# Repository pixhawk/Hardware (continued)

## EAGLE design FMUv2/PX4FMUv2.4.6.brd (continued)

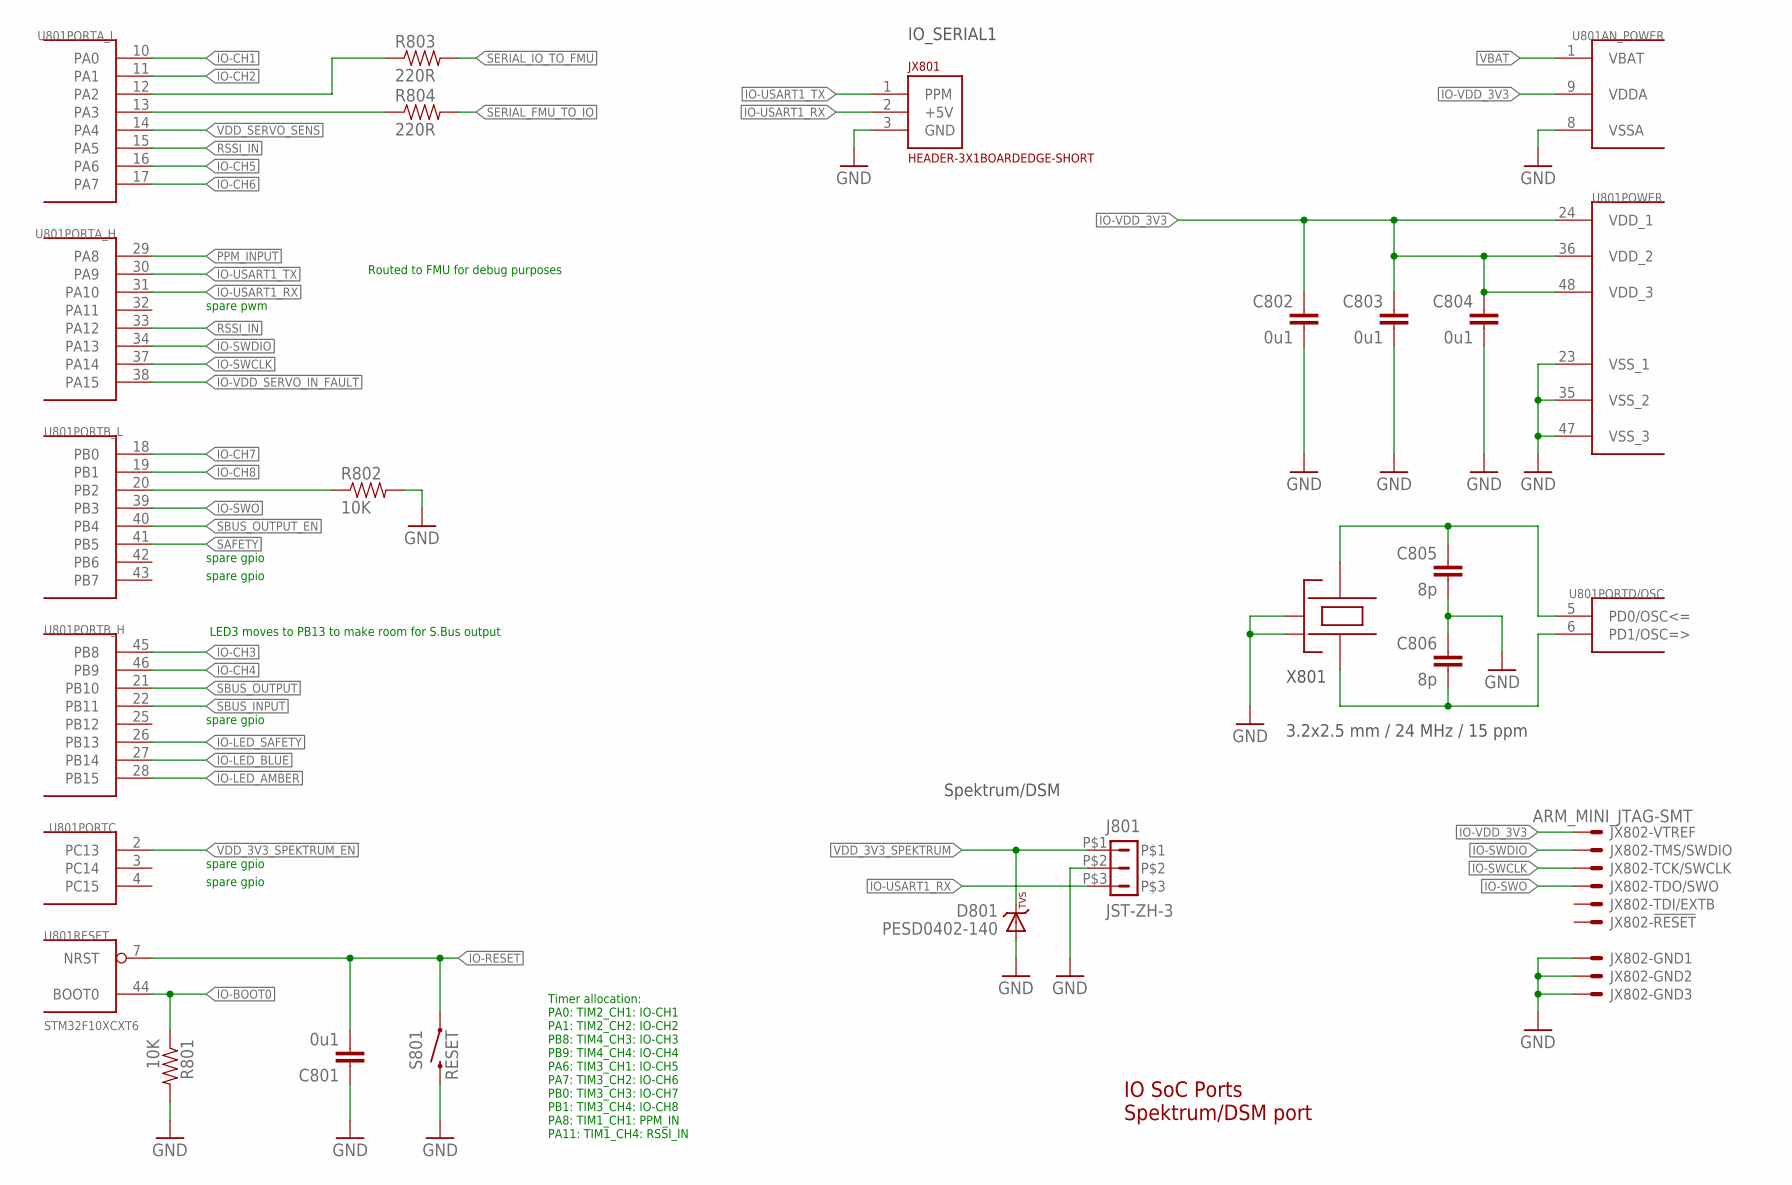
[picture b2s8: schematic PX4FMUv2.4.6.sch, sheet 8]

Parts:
C801, C802, C803, C804: 0u1; 0402-CAP; PARTNO CC0402ZRY5V7BB104
C805, C806: 8p; 0402-CAP; PARTNO C1005C0G1H080C
D801: PESD0402-140; 0402-TVS; PARTNO PESD0402-140
J801: JST-ZH-3; JST-ZH-SMT-VERTICAL; PARTNO B3B-ZR-SM4-TF (LF)(SN)(P)
JX801: HEADER-3X1BOARDEDGE-SHORT; HEADER_3X01_SMD_H_BOARD_EDGE_SHORT
JX802: ARM_MINI_JTAG-SMT; FTSH-105-01-XXX-DV-K; PARTNO M50-3900542
R801, R802: 10K; 0402-RES; PARTNO RC0402FR-0710KL
R803, R804: 220R; 0402-RES; PARTNO RC0402FR-07220RL
S801: RESET; EVQP7J01K; PARTNO EVQ-P7J01P
U801: STM32F10XCXT6; TQFP48; PARTNO STM32F100C8T6B
X801: 3.2x2.5 mm / 24 MHz / 15 ppm; OSCILLATOR-3.2X2.5; PARTNO NX3225SA-24.000000MHZ

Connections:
!IO-LED_AMBER: U801.28 (PB15); also elsewhere on the board
!IO-LED_BLUE: U801.27 (PB14); also elsewhere on the board
!IO-LED_SAFETY: U801.26 (PB13); also elsewhere on the board
!SBUS_OUTPUT_EN: U801.40 (PB4); also elsewhere on the board
GND: C801.P$1 (1), C802.P$2 (2), C803.P$2 (2), C804.P$2 (2), C805.P$2 (2), C806.P$1 (1), D801.A, J801.P$2, JX801.3 (GND), JX802.3, JX802.5, JX802.9, R801.P$2 (2), R802.P$2 (2), S801.B3 (2), U801.8 (VSSA), U801.23 (VSS_1), U801.35 (VSS_2), U801.47 (VSS_3), X801.2 (NC_2), X801.4 (NC_4); also elsewhere on the board
IO-!RESET: C801.P$2 (2), S801.A1 (1), U801.7 (NRST); also elsewhere on the board
IO-!VDD_SERVO_IN_FAULT: U801.38 (PA15); also elsewhere on the board
IO-BOOT0: R801.P$1 (1), U801.44 (BOOT0); also elsewhere on the board
IO-BOOT1: R802.P$1 (1), U801.20 (PB2)
IO-CH1: U801.10 (PA0); also elsewhere on the board
IO-CH2: U801.11 (PA1); also elsewhere on the board
IO-CH3: U801.45 (PB8); also elsewhere on the board
IO-CH4: U801.46 (PB9); also elsewhere on the board
IO-CH5: U801.16 (PA6); also elsewhere on the board
IO-CH6: U801.17 (PA7); also elsewhere on the board
IO-CH7: U801.18 (PB0); also elsewhere on the board
IO-CH8: U801.19 (PB1); also elsewhere on the board
IO-SWCLK: JX802.4, U801.37 (PA14)
IO-SWDIO: JX802.2, U801.34 (PA13)
IO-SWO: JX802.6, U801.39 (PB3)
IO-USART1_RX: J801.P$3, JX801.2 (+5V), U801.31 (PA10)
IO-USART1_TX: JX801.1 (PPM), U801.30 (PA9); also elsewhere on the board
IO-VDD_3V3: C802.P$1 (1), C803.P$1 (1), C804.P$1 (1), JX802.1, U801.9 (VDDA), U801.24 (VDD_1), U801.36 (VDD_2), U801.48 (VDD_3); also elsewhere on the board
unnamed: R803.P$1 (1), U801.12 (PA2)
unnamed: R804.P$1 (1), U801.13 (PA3)
unnamed: C806.P$2 (2), U801.6 (PD1/OSC=>), X801.1
unnamed: C805.P$1 (1), U801.5 (PD0/OSC<=), X801.3
PPM_INPUT: U801.29 (PA8); also elsewhere on the board
RSSI_IN: U801.15 (PA5), U801.33 (PA12); also elsewhere on the board
SAFETY: U801.41 (PB5); also elsewhere on the board
SBUS_INPUT: U801.22 (PB11); also elsewhere on the board
SBUS_OUTPUT: U801.21 (PB10); also elsewhere on the board
SERIAL_FMU_TO_IO: R804.P$2 (2); also elsewhere on the board
SERIAL_IO_TO_FMU: R803.P$2 (2); also elsewhere on the board
VBAT: U801.1 (VBAT); also elsewhere on the board
VDD_3V3_SPEKTRUM: D801.C, J801.P$1; also elsewhere on the board
VDD_3V3_SPEKTRUM_EN: U801.2 (PC13); also elsewhere on the board
VDD_SERVO_SENS: U801.14 (PA4); also elsewhere on the board

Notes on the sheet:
IO SoC Ports Spektrum/DSM port
LED3 moves to PB13 to make room for S.Bus output
Routed to FMU for debug purposes
IO_SERIAL1
Spektrum/DSM
Timer allocation: PA0: TIM2_CH1: IO-CH1 PA1: TIM2_CH2: IO-CH2 PB8: TIM4_CH3: IO-CH3 PB9: TIM4_CH4: IO-CH4 PA6: TIM3_CH1: IO-CH5 PA7: TIM3_CH2: IO-CH6 PB0: TIM3_CH3: IO-CH7 PB1: TIM3_CH4: IO-CH8 PA8: TIM1_CH1: PPM_IN PA11: TIM1_CH4: RSSI_IN
spare pwm
spare gpio

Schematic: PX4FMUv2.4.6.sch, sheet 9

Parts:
C901, C902, C903: 0u1; 0402-CAP; PARTNO CC0402ZRY5V7BB104
D901, D902, D903: PESD0402-140; 0402-TVS; PARTNO PESD0402-140
D904: MSS1P4-M3; MICROSMP; PARTNO MSS1P4-M3/89A
J901: HEADER-3X163X16RA; 3X16RA
L901: KNH16C104DA5TS; KYOCERA-KNH16-DA; PARTNO KNH16C104DA5TS
R901: 10K; 0402-RES; PARTNO RC0402FR-0710KL
R902, R903, R904, R905, R906, R907, R908, R909, R910, R911, R912, R913, R914, R915, R916, R917: 220R; 0402-RES; PARTNO RC0402FR-07220RL
R918, R919, R922: 10K/0.1%; 0402-RES; PARTNO ERA-2AEB103X
U901, U902: TXS0108QFN20; QFN20-RGY; PARTNO TXS0108ERGYR
U903: 74LVC2G240; TSSOP8_SOT505-2; PARTNO 74LVC2G240DP,125

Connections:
!SBUS_OUTPUT_EN: U903.7 (!2OE); also elsewhere on the board
FMU-CH1: U901.7 (A6); also elsewhere on the board
FMU-CH1-PROT: J901.46, R913.P$2 (2)
FMU-CH2: U901.6 (A5); also elsewhere on the board
FMU-CH3: U901.5 (A4); also elsewhere on the board
FMU-CH4: U901.4 (A3); also elsewhere on the board
FMU-CH5: U901.3 (A2); also elsewhere on the board
FMU-CH6: U901.1 (A1); also elsewhere on the board
FMU-CH6-PROT: J901.31, R902.P$2 (2)
FMU-VDD_3V3: C902.P$1 (1), U901.2 (VCCA), U901.10 (OE), U901.19 (VCCB); also elsewhere on the board
GND: C901.P$2 (2), C902.P$2 (2), C903.P$2 (2), D901.A, D902.A, D903.A, J901.3, J901.6, J901.9, J901.12, J901.15, J901.18, J901.21, J901.24, J901.27, J901.30, J901.33, J901.36, J901.39, J901.42, J901.45, J901.48, L901.P$3, L901.P$4, L901.P$5, R919.P$1 (1), U901.11 (GND), U902.11 (GND), U903.1 (!1OE), U903.4 (GND); also elsewhere on the board
IO-CH1: U902.9 (A8); also elsewhere on the board
IO-CH1-PROT: J901.28, R917.P$2 (2)
IO-CH2: U902.8 (A7); also elsewhere on the board
IO-CH3: U902.7 (A6); also elsewhere on the board
IO-CH4: U902.6 (A5); also elsewhere on the board
IO-CH5: U902.5 (A4); also elsewhere on the board
IO-CH6: U902.4 (A3); also elsewhere on the board
IO-CH7: U902.3 (A2); also elsewhere on the board
IO-CH8: U902.1 (A1); also elsewhere on the board
IO-CH8-PROT: J901.7, R905.P$2 (2)
IO-VDD_3V3: C901.P$1 (1), C903.P$1 (1), U902.2 (VCCA), U902.10 (OE), U902.19 (VCCB), U903.8 (VCC); also elsewhere on the board
IO-VDD_5V5: J901.2; also elsewhere on the board
unnamed: R918.P$2 (2), R922.P$1 (1)
unnamed: J901.10, R914.P$2 (2)
unnamed: D902.C, R901.P$2 (2), R910.P$1 (1), U903.3 (2Y)
unnamed: R905.P$1 (1), U902.20 (B1)
unnamed: R914.P$1 (1), U902.18 (B2)
unnamed: R906.P$1 (1), U902.17 (B3)
unnamed: R915.P$1 (1), U902.16 (B4)
unnamed: R907.P$1 (1), U902.15 (B5)
unnamed: R916.P$1 (1), U902.14 (B6)
unnamed: R908.P$1 (1), U902.13 (B7)
unnamed: R917.P$1 (1), U902.12 (B8)
unnamed: R902.P$1 (1), U901.20 (B1)
unnamed: R911.P$1 (1), U901.18 (B2)
unnamed: R903.P$1 (1), U901.17 (B3)
unnamed: R912.P$1 (1), U901.16 (B4)
unnamed: R904.P$1 (1), U901.15 (B5)
unnamed: R913.P$1 (1), U901.14 (B6)
unnamed: J901.34, R911.P$2 (2)
unnamed: J901.13, R906.P$2 (2)
unnamed: J901.16, R915.P$2 (2)
unnamed: J901.19, R907.P$2 (2)
unnamed: J901.22, R916.P$2 (2)
unnamed: J901.25, R908.P$2 (2)
unnamed: J901.37, R903.P$2 (2)
unnamed: J901.40, R912.P$2 (2)
unnamed: J901.43, R904.P$2 (2)
unnamed: J901.4, R910.P$2 (2)
unnamed: D903.C, D904.CATHODE (C), L901.P$1
PPM-SBUS-PROT: J901.1, R909.P$2 (2)
PPM_INPUT: D901.C, R909.P$1 (1), U903.2 (1A); also elsewhere on the board
RSSI_IN: R901.P$1 (1); also elsewhere on the board
SBUS_INPUT: U903.6 (1Y); also elsewhere on the board
SBUS_OUTPUT: U903.5 (2A); also elsewhere on the board
VDD_SERVO: D904.ANODE (A), J901.5, J901.8, J901.11, J901.14, J901.17, J901.20, J901.23, J901.26, J901.29, J901.32, J901.35, J901.38, J901.41, J901.44, J901.47, R922.P$2 (2); also elsewhere on the board
VDD_SERVO_IN: L901.P$2; also elsewhere on the board
VDD_SERVO_SENS: R918.P$1 (1), R919.P$2 (2); also elsewhere on the board

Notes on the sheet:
Servo Header S.Bus interface
S.Bus in/out
Servo outputs

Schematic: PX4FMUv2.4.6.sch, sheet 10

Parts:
C1001: 10u/25V; 0805-CAP; PARTNO CL21A106KAYNNNE
C1002: 10n; 0402-CAP; PARTNO CC0402KRX7R7BB103
C1003: 1u; 0603-CAP; PARTNO CC0603ZRY5V7BB105
C1004: 10u; 0603-CAP; PARTNO C1608X5R1A106K080AC
C1005: 0u1; 0402-CAP; PARTNO CC0402ZRY5V7BB104
C1008: 2u2; 0402-CAP; PARTNO C1005X6S1C225K050BC
D1001: PMEG2005CT; SOT23-3; PARTNO PMEG2005CT
F1001: 0ZCA0035FF2G; PTC-1206; PARTNO 0ZCA0035FF2G
R1001: 100K; 0402-RES; PARTNO RC0402FR-07100KL
R1002: 10K; 0402-RES; PARTNO RC0402FR-0710KL
U1001: BQ24313; QFN8-DSG; PARTNO BQ24313DSGT
U1002: MIC5332; MLF-8-EPAD; PARTNO MIC5332-SSYMT

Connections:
GND: C1001.P$2 (2), C1002.P$2 (2), C1003.P$2 (2), C1004.P$2 (2), C1005.P$2 (2), C1008.P$2 (2), R1001.P$1 (1), R1002.P$1 (1), U1001.2 (VSS), U1001.5 (!CE), U1001.6 (VBAT), U1001.GND (VSS), U1001.P$2 (VSS), U1001.P$3 (VSS), U1002.2 (GND), U1002.GND; also elsewhere on the board
IO-!RESET: U1002.3 (POR2); also elsewhere on the board
IO-!VDD_SERVO_IN_FAULT: U1001.4 (!FAULT); also elsewhere on the board
IO-VDD_3V3: C1003.P$1 (1), C1004.P$1 (1), U1002.7 (VOUT2); also elsewhere on the board
IO-VDD_5V5: C1001.P$1 (1), C1005.P$1 (1), D1001.3 (CC), U1002.1 (VIN), U1002.4 (EN2); also elsewhere on the board
unnamed: D1001.2 (A2), U1001.8 (OUT)
unnamed: R1001.P$2 (2), U1001.7 (ILIM)
unnamed: D1001.1 (A1), F1001.2
unnamed: C1002.P$1 (1), U1002.6 (CSET)
VDD_3V3_SPEKTRUM: C1008.P$1 (1), U1002.8 (VOUT1); also elsewhere on the board
VDD_3V3_SPEKTRUM_EN: R1002.P$2 (2), U1002.5 (EN1); also elsewhere on the board
VDD_5V_IN: F1001.1; also elsewhere on the board
VDD_SERVO_IN: U1001.1 (IN); also elsewhere on the board

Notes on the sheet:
Dual supply from servo rail and FMU 5V rail
Current limit = 25 / Rilim (current in A, R in kOhms) 100K = 250mA
IO Power Supply
Reset output 1s / uF 10n = 10ms delay from power good to reset de-asserted.
Output voltage limited to 5.5V for input voltages up to 10.5V; output switches off at higher input voltages.

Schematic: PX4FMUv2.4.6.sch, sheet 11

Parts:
C1101, C1102, C1103: 22u/25V; 0805-CAP; PARTNO CL21A226MAQNNNE
C1104: 100u; 1206-CAP; PARTNO C3216X5R1A107M160AC
C1105, C1106, C1107: 0u1; 0402-CAP; PARTNO C1005X7R1E104K050BB
C1108, C1109, C1110: 10p/25V; 0402-CAP; PARTNO C0402C100J3GACTU
J601: DF13C-6P-1.25V; PARTNO DF13C-6P-1.25V(20)
L1101, L1102: KNH16C104DA5TS; KYOCERA-KNH16-DA; PARTNO KNH16C104DA5TS
R1101, R1102: 10K/0.1%; 0402-RES; PARTNO ERA-2AEB103X
R1103, R1104: 1M; 0402-RES; PARTNO RC0402FR-071ML
R1105, R1109, R1112: 453K; 0402-RES; PARTNO RMCF0402FT453K
R1106, R1110, R1113: 56K; 0402-RES; PARTNO ERA-2AEB563X
R1107, R1111, R1114: 105K; 0402-RES; PARTNO ERJ-2RKF1053X
R1115: 0R; 0402-RES; PARTNO ERJ-2GE0R00X
RN1101: 1M; EXB28V; PARTNO EXB-28V105JX
U1101: LTC4417; MO-220; PARTNO LTC4417IUF#PBF
U1102, U1103, U1104: NTHD4102PT1G; 1206-8; PARTNO NTHD4102PT1G

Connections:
!VBUS_VALID: RN1101.2 (1), U1101.P$9 (!VALID3); also elsewhere on the board
!VDD_BRICK_VALID: RN1101.4 (1), U1101.P$7 (!VALID1); also elsewhere on the board
!VDD_SERVO_VALID: RN1101.3 (1), U1101.P$8 (!VALID2); also elsewhere on the board
BATT_CURRENT_SENS: R1101.P$1 (1); also elsewhere on the board
BATT_CURRENT_SENS_PROT: J601.3, L1101.P$1, R1104.P$1 (1)
BATT_VOLTAGE_SENS: R1102.P$1 (1); also elsewhere on the board
BATT_VOLTAGE_SENS_PROT: J601.4, L1102.P$1, R1103.P$1 (1)
GND: C1101.P$2 (2), C1102.P$2 (2), C1103.P$2 (2), C1104.P$2 (2), C1105.P$2 (2), C1106.P$2 (2), C1107.P$2 (2), C1108.P$2 (2), C1109.P$2 (2), C1110.P$2 (2), J601.5, J601.6, L1101.P$3, L1101.P$4, L1101.P$5, L1102.P$3, L1102.P$4, L1102.P$5, R1103.P$2 (2), R1104.P$2 (2), R1107.P$2 (2), R1111.P$2 (2), R1114.P$2 (2), R1115.P$1 (1), U1101.P$10 (GND), U1101.P$25 (GND); also elsewhere on the board
unnamed: C1108.P$1 (1), R1105.P$2 (2), R1106.P$1 (1), U1101.P$1 (UV1)
unnamed: R1106.P$2 (2), R1107.P$1 (1), U1101.P$2 (OV1)
unnamed: C1109.P$1 (1), R1109.P$2 (2), R1110.P$1 (1), U1101.P$3 (UV2)
unnamed: R1110.P$2 (2), R1111.P$1 (1), U1101.P$4 (OV2)
unnamed: R1113.P$2 (2), R1114.P$1 (1), U1101.P$6 (OV3)
unnamed: C1110.P$1 (1), R1112.P$2 (2), R1113.P$1 (1), U1101.P$5 (UV3)
unnamed: C1105.P$1 (1), U1101.P$18 (VS1), U1102.P$1 (S), U1102.P$3 (S)
unnamed: L1102.P$2, R1102.P$2 (2)
unnamed: L1101.P$2, R1101.P$2 (2)
unnamed: R1115.P$2 (2), U1101.P$24 (HYS)
unnamed: C1106.P$1 (1), U1101.P$16 (VS2), U1103.P$1 (S), U1103.P$3 (S)
unnamed: C1107.P$1 (1), U1101.P$14 (VS3), U1104.P$1 (S), U1104.P$3 (S)
unnamed: U1101.P$13 (G3), U1104.P$2 (G), U1104.P$4 (G)
unnamed: U1101.P$15 (G2), U1103.P$2 (G), U1103.P$4 (G)
unnamed: U1101.P$17 (G1), U1102.P$2 (G), U1102.P$4 (G)
VBUS: C1103.P$1 (1), R1112.P$1 (1), U1101.P$19 (V3), U1104.P$7 (D), U1104.P$8 (D); also elsewhere on the board
VDD_5V_BRICK: C1101.P$1 (1), J601.1, J601.2, R1105.P$1 (1), U1101.P$21 (V1), U1102.P$7 (D), U1102.P$8 (D); also elsewhere on the board
VDD_5V_IN: C1104.P$1 (1), RN1101.5 (2), RN1101.6 (2), RN1101.7 (2), U1101.P$12 (VOUT), U1102.P$5 (D), U1102.P$6 (D), U1103.P$5 (D), U1103.P$6 (D), U1104.P$5 (D), U1104.P$6 (D); also elsewhere on the board
VDD_SERVO: C1102.P$1 (1), R1109.P$1 (1), U1101.P$20 (V2), U1103.P$7 (D), U1103.P$8 (D); also elsewhere on the board

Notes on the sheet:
Power source selector
Resistors picked so that undervoltage lockout starts at 4.0V and overvoltage lockout at 5.75V. Use 1% or better accuracy!
POWER PATH CONTROLLER: Does enable output if valid for continous 256 ms
XXX Check all input pins are 5V tolerant. Hooking this up to a 3.3V rail would make the lines non-readable during power-up sequencing

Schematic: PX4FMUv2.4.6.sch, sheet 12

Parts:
!VBUS_VALID: PAD.04; PAD.04X.04; PARTNO *
!VDD_BRICK_VALID: PAD.04; PAD.04X.04; PARTNO *
!VDD_SERVO_VALID: PAD.04; PAD.04X.04; PARTNO *
ADC_PR: PAD.04; PAD.04X.04; PARTNO *
CAN_H: PAD.04; PAD.04X.04; PARTNO *
CAN_L: PAD.04; PAD.04X.04; PARTNO *
FMU-BOOT1101: PAD.04; PAD.04X.04; PARTNO *
GND, GND.: PAD.04; PAD.04X.04; PARTNO *
IO-BOOT1101: PAD.04; PAD.04X.04; PARTNO *
JP1, JP2: FIDUCIAL1.5X3; FIDUCIAL-1.5X3; PARTNO *
M3_MOUNT1101, M3_MOUNT1102, M3_MOUNT1103, M3_MOUNT1104: MOUNT-HOLE3.1MM; MOUNT-HOLE3.1; PARTNO *
OSHW_LOGO: OSHW-LOGOS; OSHW-LOGO-S; PARTNO *
S1RX, S1TX, S2RX, S2TX, S3RX, S3TX, S4RX, S4TX, S5_RX, S5_TX: PAD.04; PAD.04X.04; PARTNO *
VBUS: PAD.04; PAD.04X.04; PARTNO *
VDDA_3V1101: PAD.04; PAD.04X.04; PARTNO *
VDD_3V1101, VDD_5V_BRICK, VDD_5V_IN: PAD.04; PAD.04X.04; PARTNO *
VDD_SERVO: PAD.04; PAD.04X.04; PARTNO *

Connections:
!VBUS_VALID: !VBUS_VALID.P$1; also elsewhere on the board
!VDD_BRICK_VALID: !VDD_BRICK_VALID.P$1; also elsewhere on the board
!VDD_SERVO_VALID: !VDD_SERVO_VALID.P$1; also elsewhere on the board
CAN_H: CAN_H.P$1; also elsewhere on the board
CAN_L: CAN_L.P$1; also elsewhere on the board
FMU-BOOT0: FMU-BOOT1101.P$1; also elsewhere on the board
FMU-VDD_3V3: VDD_3V1101.P$1; also elsewhere on the board
GND: GND.P$1, GND..P$1; also elsewhere on the board
IO-BOOT0: IO-BOOT1101.P$1; also elsewhere on the board
PRESSURE_SENS_IN: ADC_PR.P$1; also elsewhere on the board
SERIAL1_RX: S1RX.P$1; also elsewhere on the board
SERIAL1_TX: S1TX.P$1; also elsewhere on the board
SERIAL2_RX: S2RX.P$1; also elsewhere on the board
SERIAL2_TX: S2TX.P$1; also elsewhere on the board
SERIAL3_RX: S3RX.P$1; also elsewhere on the board
SERIAL3_TX: S3TX.P$1; also elsewhere on the board
SERIAL4_RX: S4RX.P$1; also elsewhere on the board
SERIAL4_TX: S4TX.P$1; also elsewhere on the board
SERIAL5_RX: S5_RX.P$1; also elsewhere on the board
SERIAL5_TX: S5_TX.P$1; also elsewhere on the board
VBUS: VBUS.P$1; also elsewhere on the board
VDD_3V3_SENSORS: VDDA_3V1101.P$1; also elsewhere on the board
VDD_5V_BRICK: VDD_5V_BRICK.P$1; also elsewhere on the board
VDD_5V_IN: VDD_5V_IN.P$1; also elsewhere on the board
VDD_SERVO: VDD_SERVO.P$1; also elsewhere on the board

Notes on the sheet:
Mounting holes to suit M3 fastener
and Richco R908 series spacer.
Use R908-5 spacers to stack with
other PX4 series boards (7.95 mm).
Production Testing Pads
Test and Fiducials
Minimum drill: 0.3 mm
Minimum trace width (use mm for traces): 0.15 mm
Minimum copper distance (all signals): 0.15 mm
Dimension / hole minimum distance: 0.2 mm
Layout grid: 4 mil, part grid: 4 mil. Dimensions / hole positions: 0.5 mm
Board: FR4 black, 1.0 mm. Solder stop on vias < 0.6 mm.
Signoff rules: Footprint checked, pinmap checked, schematic checked, cross-references to other pages checked.
Routing: 1: general/escape 2: ground 3: horizontal 4: vertical 5: power 6: general/escape
Fiducials for machine vision alignment.
Parts: Resistors: 0402 / 1% unless specified otherwise Capacitors: 0402 to 1206, ceramic, voltage rating: 10V unless specified
COMMS
POWER
STATUS AND ANALOG

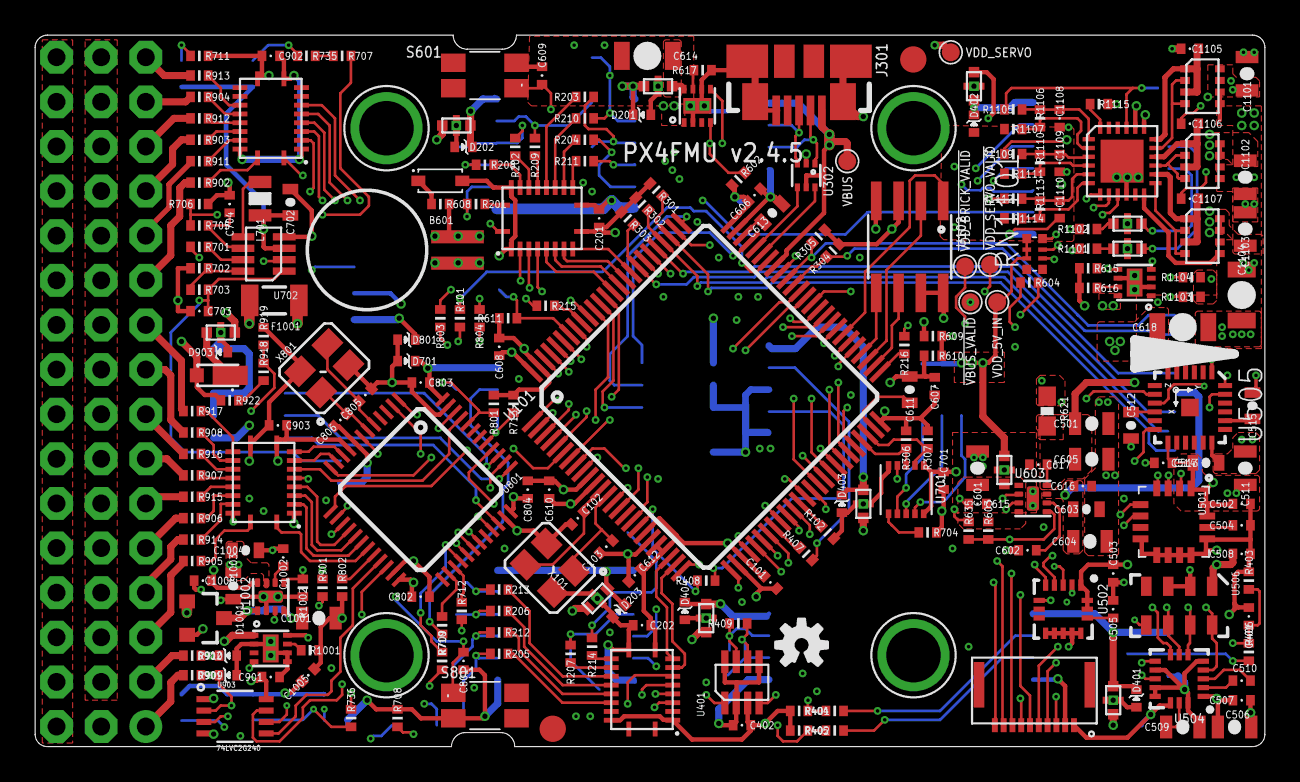
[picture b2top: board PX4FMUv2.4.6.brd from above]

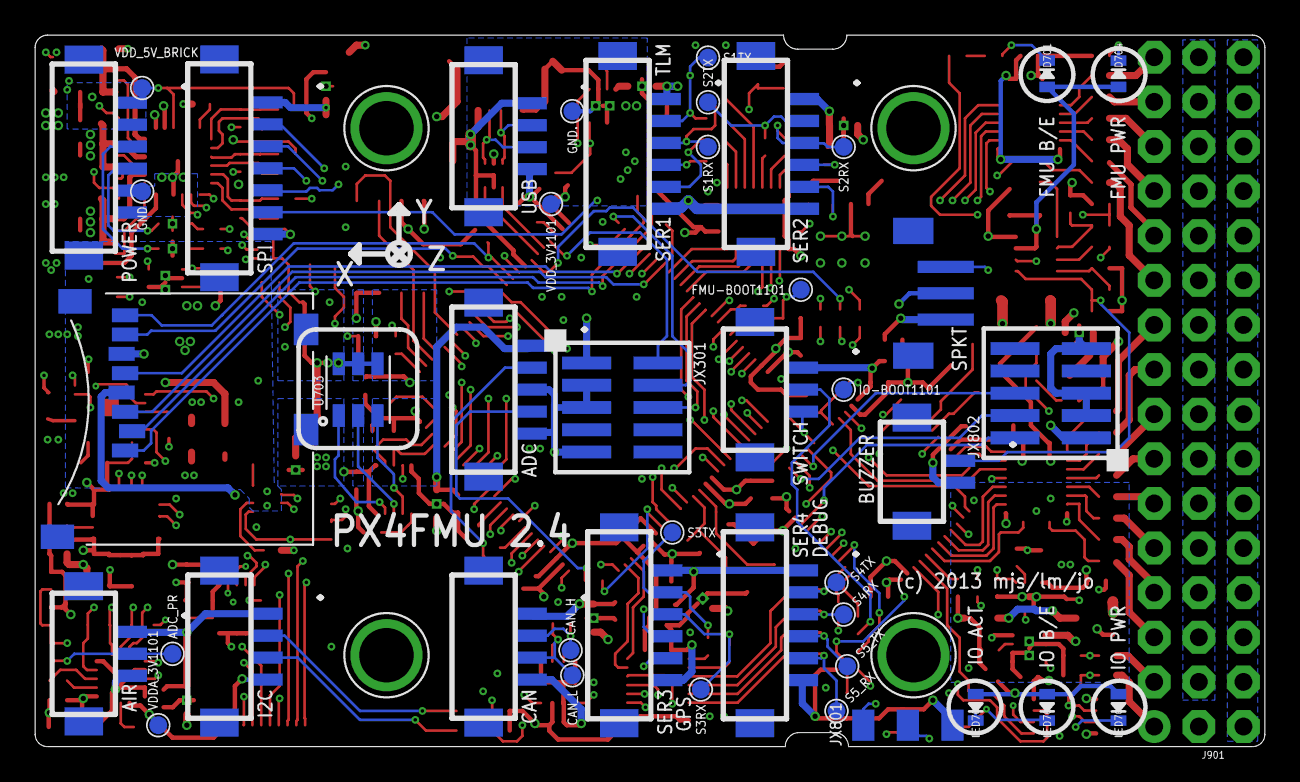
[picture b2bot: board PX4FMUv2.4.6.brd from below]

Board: 6 copper layers, 70.0 x 40.5 mm, 290 parts (45 on the bottom side), 260 nets.

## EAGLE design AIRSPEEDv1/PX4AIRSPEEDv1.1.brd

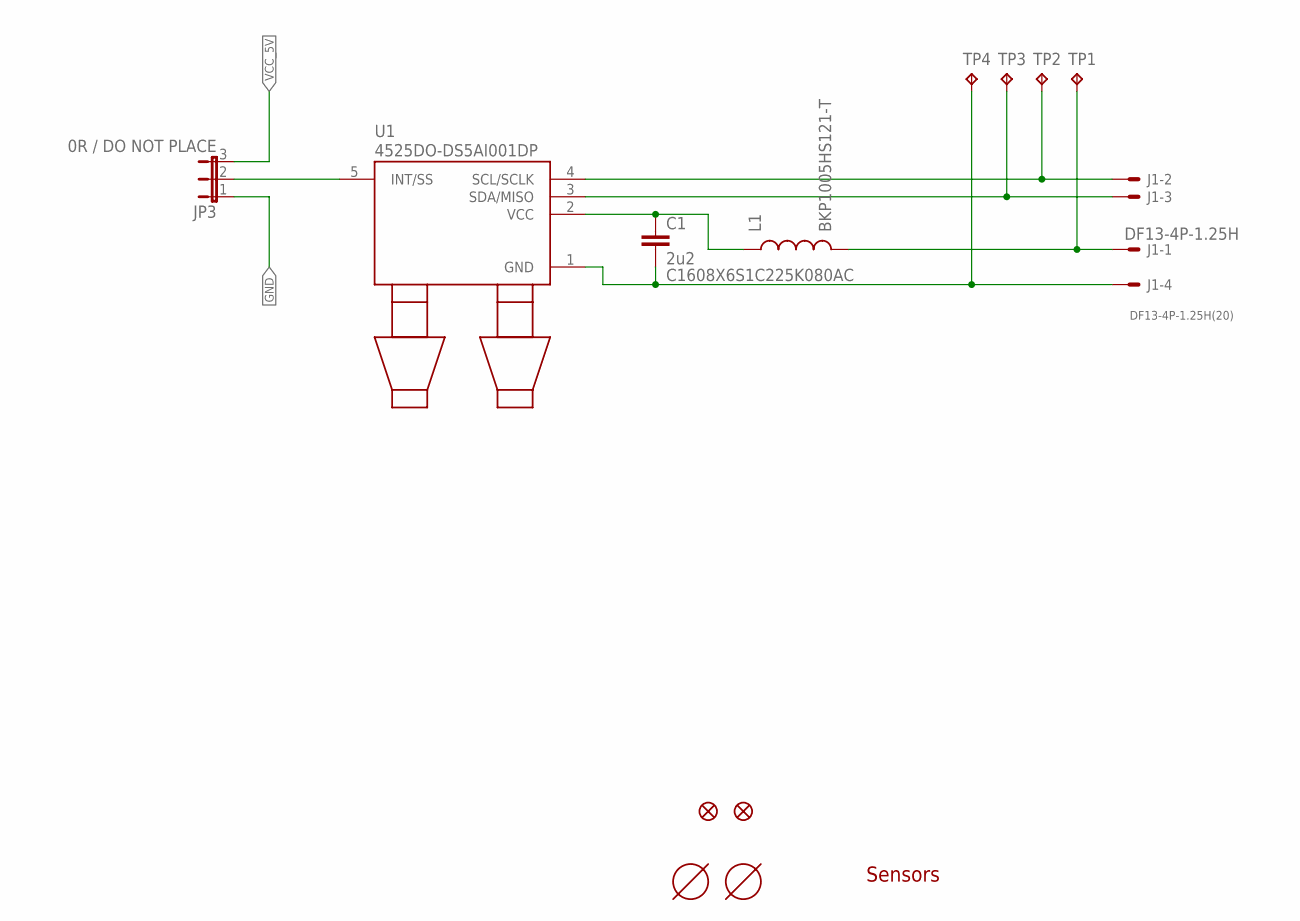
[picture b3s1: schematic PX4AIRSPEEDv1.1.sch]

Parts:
C1: 2u2; 0603-CAP; PARTNO C1608X6S1C225K080AC
J1: DF13-4P-1.25H; DF13A-4P-1.25H; PARTNO DF13-4P-1.25H(20)
JP1, JP2: FIDUCIAL1X2; FIDUCIAL-1X2; PARTNO *
JP3: 0R / DO NOT PLACE; SJ_3_0603_PASTE1&2; PARTNO *
L1: BKP1005HS121-T; 0402-IND; PARTNO BKP1005HS121-T
TP1, TP2, TP3, TP4: TPTP15R; TP15R; PARTNO *
U1: 4525DO-DS5AI001DP; PARTNO 4525DO-DS5AI001DP
U$2, U$4: MOUNT-HOLE3.1MM; MOUNT-HOLE3.1; PARTNO *

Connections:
GND: C1.P$2 (2), J1.4, JP3.1, TP4.TP, U1.1 (GND)
unnamed: J1.2, TP2.TP, U1.4 (SCL/SCLK)
unnamed: J1.3, TP3.TP, U1.3 (SDA/MISO)
unnamed: J1.1, L1.P$2 (2), TP1.TP
unnamed: JP3.2, U1.5 (INT/SS)
VCC_5V: C1.P$1 (1), JP3.3, L1.P$1 (1), U1.2 (VCC)

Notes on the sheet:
Sensors

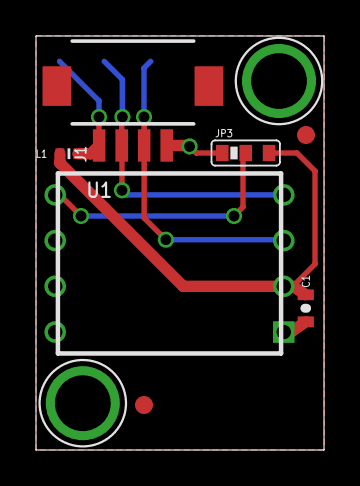
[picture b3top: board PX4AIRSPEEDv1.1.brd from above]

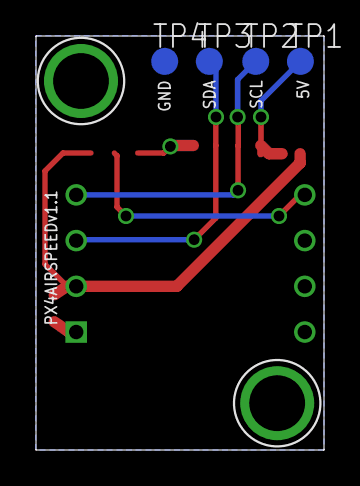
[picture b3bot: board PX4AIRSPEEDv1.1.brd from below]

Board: 4 copper layers, 16.0 x 23.0 mm, 13 parts (4 on the bottom side), 6 nets.

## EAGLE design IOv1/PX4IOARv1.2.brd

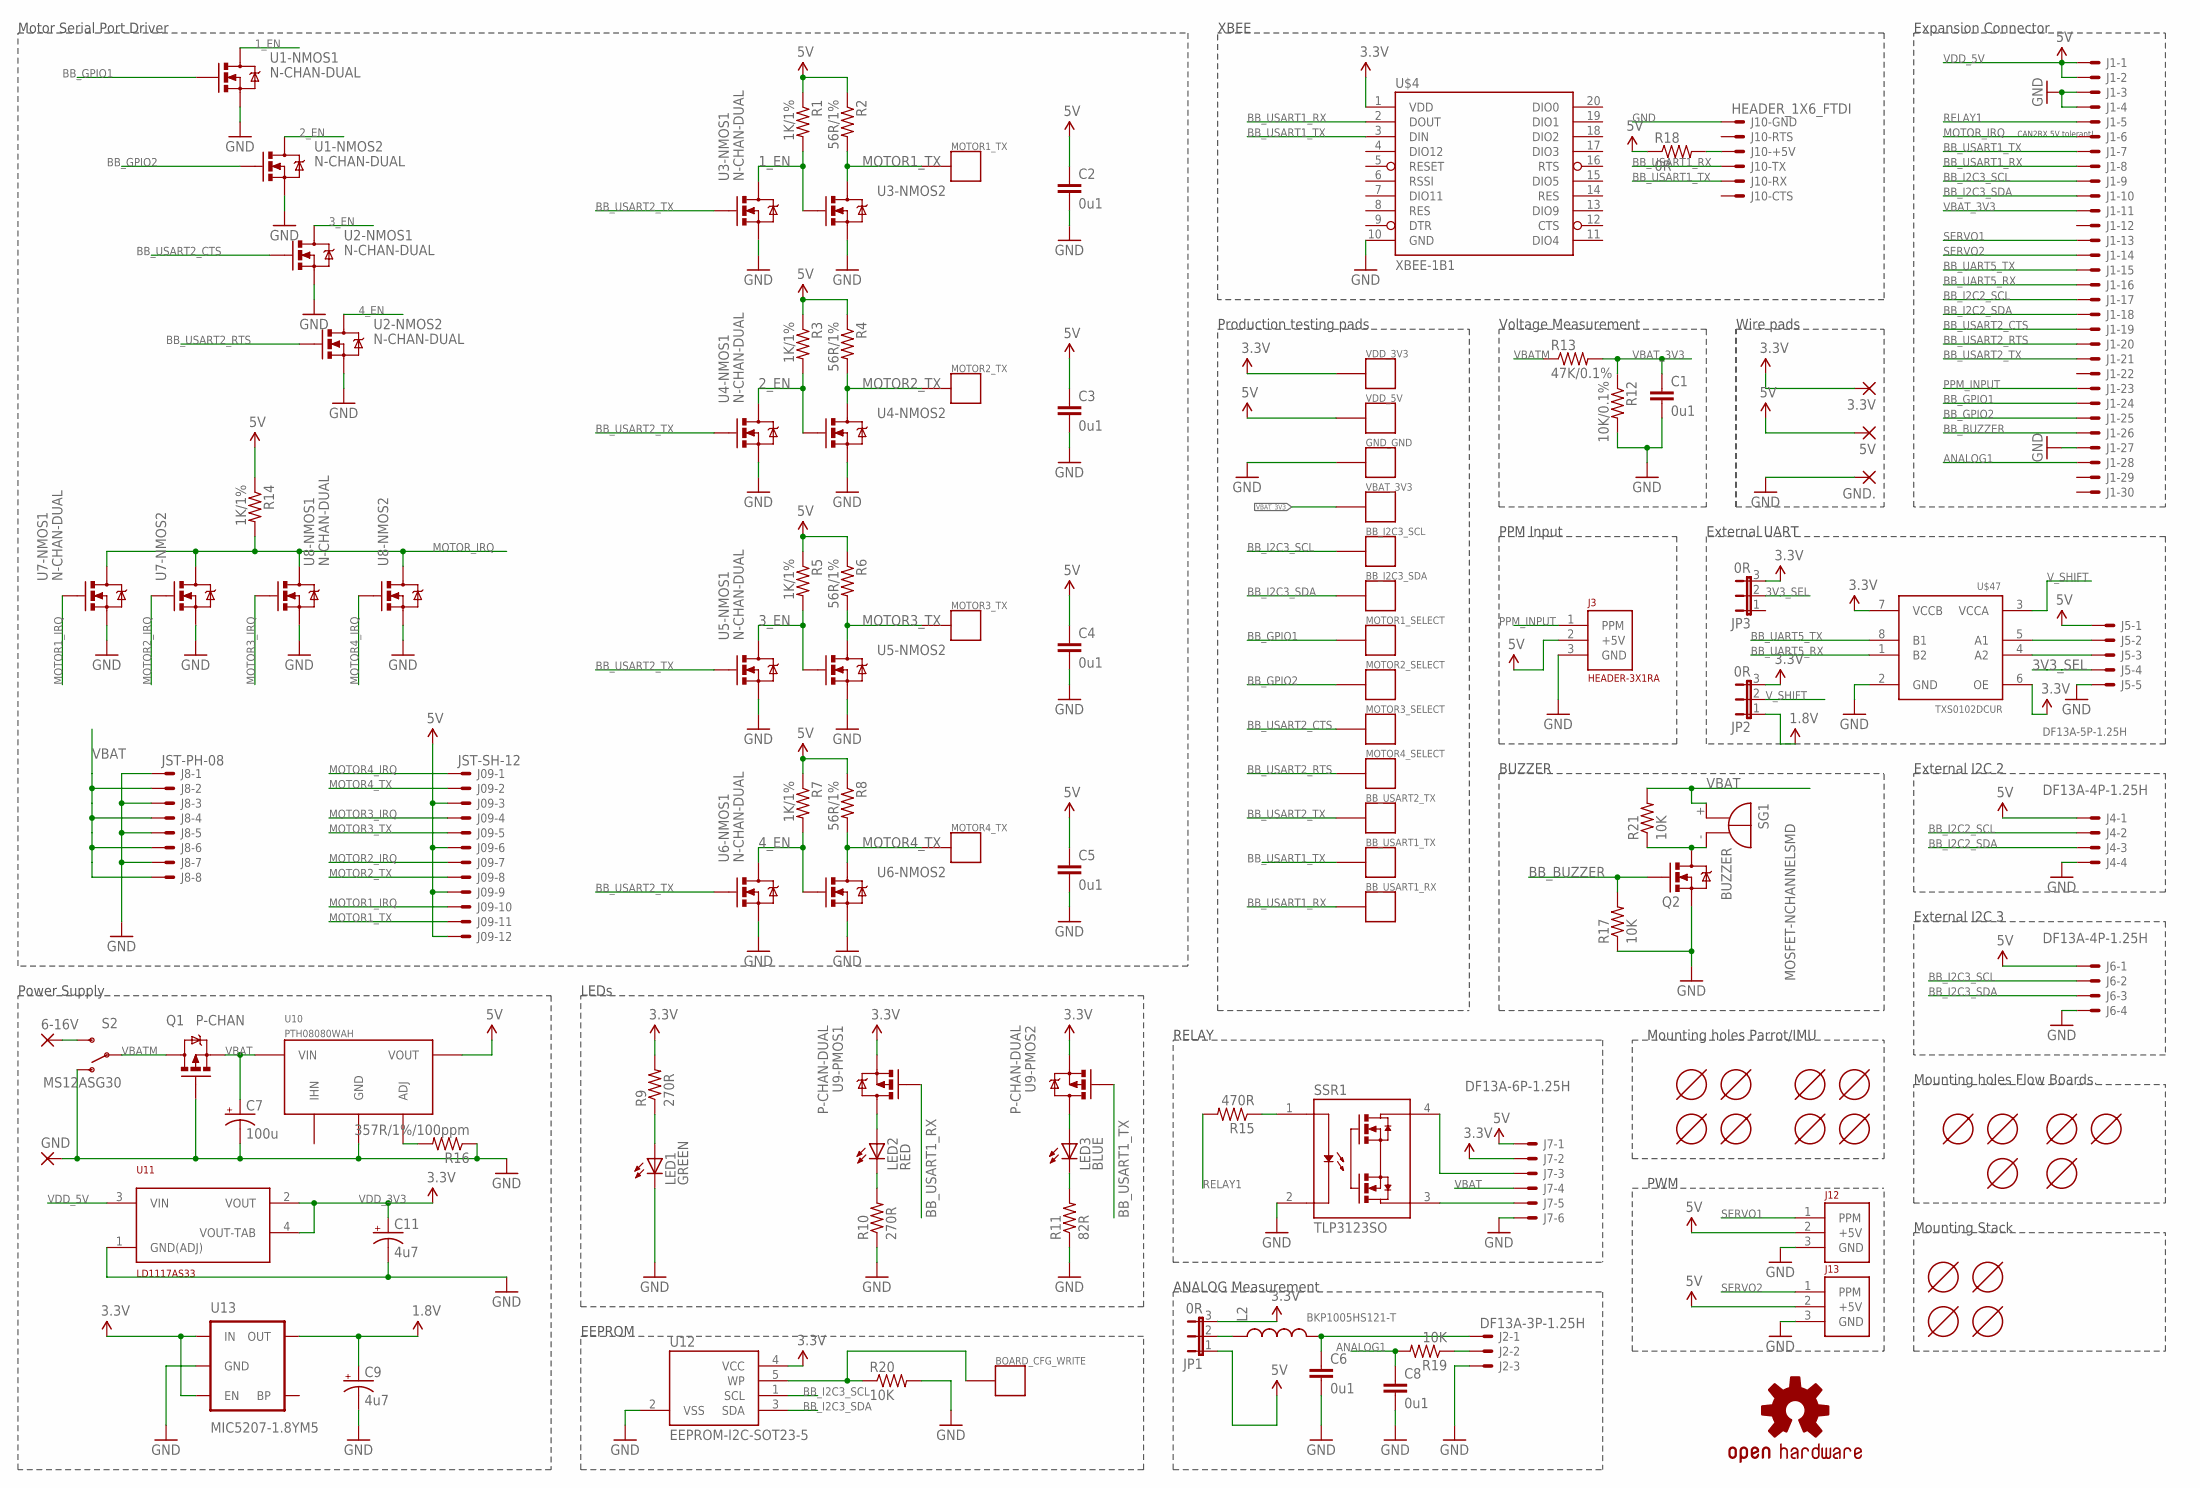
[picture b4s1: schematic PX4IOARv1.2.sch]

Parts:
3.3V, 5V: WIREPADSMD3,5-2; 3,5-2
6-16V: WIREPADTH-2.0MM; WIREPAD-TH-2.0MM
BB_I2C3_SCL, BB_I2C3_SDA: PAD.05; PAD.05X.05
BB_USART1_RX, BB_USART1_TX, BB_USART2_TX: PAD.05; PAD.05X.05
BOARD_CFG_WRITE: PAD.05; PAD.05X.05
C1, C2, C3, C4, C5, C6, C8: 0u1; 0402-CAP; PARTNO CC0402ZRY5V7BB104
C7: 100u; EIA7343; PARTNO T491X107K025ZT
C9, C11: 4u7; EIA3216; PARTNO T491A475K010AT
GND: WIREPADTH-2.0MM; WIREPAD-TH-2.0MM
GND.: WIREPADSMD3,5-2; 3,5-2
GND_GND: PAD.05; PAD.05X.05
J1: HEADER_2X15-REV; HEADER_2MM_2X15_REVERSE; PARTNO 951230-2520-AR-PR
J2: DF13A-3P-1.25H; PARTNO DF13A-3P-1.25H(20)
J3: HEADER-3X1RA; 3X1RA
J4, J6: DF13A-4P-1.25H; PARTNO DF13A-4P-1.25H(20)
J5: DF13A-5P-1.25H; PARTNO DF13A-5P-1.25H(20)
J7: DF13A-6P-1.25H; PARTNO DF13A-6P-1.25H(20)
J8: JST-PH-08; B8B-PH-K-S; PARTNO B8B-PH-K-S(LF)(SN)
J09: JST-SH-12; SM12B-SRSS-TB; PARTNO SM12B-SRSS-TB(LF)(SN)
J10: HEADER_1X6_FTDI; HEADER_1X06-FTDI
J12, J13: HEADER-3X1SMD-BOARDEDGE; HEADER_3X01_SMD_H_BOARD_EDGE; PARTNO *
JP1, JP2, JP3: 0R; SJ_3_0603_PASTE1&2; PARTNO RMCF0402ZT0R00
L2: BKP1005HS121-T; 0402-IND; PARTNO BKP1005HS121-T
LED1: GREEN; LED-0603; PARTNO LNJ337W83RA
LED2: RED; LED-0603; PARTNO LNJ237W82RA
LED3: BLUE; LED-0603; PARTNO LNJ937W8CRA
MOTOR1_SELECT, MOTOR1_TX, MOTOR2_SELECT, MOTOR2_TX, MOTOR3_SELECT, MOTOR3_TX, MOTOR4_SELECT, MOTOR4_TX: PAD.05; PAD.05X.05
Q1: P-CHAN; DPAK; PARTNO IRFR5505TRPBF
Q2: MOSFET-NCHANNELSMD; SOT23-3; PARTNO ZXMS6004FFTA
R1, R3, R5, R7, R14: 1K/1%; 0402-RES; PARTNO RMCF0402FT1K00
R2, R4, R6, R8: 56R/1%; 0402-RES; PARTNO ERJ-2RKF56R0X
R9, R10: 270R; 0402-RES; PARTNO RC0402JR-07270RL
R11: 82R; 0402-RES; PARTNO RC0402JR-0782RL
R12: 10K/0.1%; 0402-RES; PARTNO ERA-2AEB103X
R13: 47K/0.1%; 0402-RES; PARTNO ERA-2AEB473X
R15: 470R; 0402-RES; PARTNO RC0402JR-07470RL
R16: 357R/1%/100ppm; 0402-RES; PARTNO ERJ-2RKF3570X
R17, R19, R20, R21: 10K; 0402-RES; PARTNO RMCF0402FT10K0
R18: 0R; 0402-RES; PARTNO RMCF0402ZT0R00
S2: MS12ASG30; SWITCH-SPDT-TH-HORZ; PARTNO MS12ASG30
SG1: BUZZER; F/TMB; PARTNO PKM13EPYH4000-A0
SSR1: TLP3123SO; SOP4-2.54; PARTNO TLP3123(F)
U1, U2, U3, U4, U5, U6, U7, U8: N-CHAN-DUAL; SOT363_PHILIPS; PARTNO 2N7002PS,115
U9: P-CHAN-DUAL; SOT363_PHILIPS; PARTNO BSS84DW-7-F
U10: PTH08080WAH; PTH08080W_TH; PARTNO PTH08080WAH
U11: LD1117AS33; SOT-223; PARTNO LD1117AS33
U12: EEPROM-I2C-SOT23-5; SOT23-5; PARTNO 24LC01BT-I/OT
U13: MIC5207-1.8YM5; SOT23-5; PARTNO MIC5207-1.8YM5
U$1, U$8, U$31, U$32, U$33, U$34: MOUNT-HOLE2.6MM; MOUNT-HOLE2.6
U$4: XBEE-1B1; XBEE-1; PARTNO NPPN101BFCN-RC
U$6, U$7, U$17, U$19, U$21, U$29, U$30, U$40, U$43, U$44, U$45, U$46: MOUNT-HOLE3.1MM; MOUNT-HOLE3.1
U$9: OSHW-LOGOM; OSHW-LOGO-M
U$47: TXS0102DCUR; TI-DCU; PARTNO TXS0102DCUR
VBAT_3V3: PAD.05; PAD.05X.05
VDD_3V3, VDD_5V: PAD.05; PAD.05X.05

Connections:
1_EN: R1.2, U1.6 (D), U3.5 (G), U3.6 (D)
2_EN: R3.2, U1.3 (D), U4.5 (G), U4.6 (D)
3V3_SEL: J5.4, JP3.2
3_EN: R5.2, U2.6 (D), U5.5 (G), U5.6 (D)
4_EN: R7.2, U2.3 (D), U6.5 (G), U6.6 (D)
ANALOG1: C8.1, J1.28, R19.2
BB_BUZZER: J1.26, Q2.1 (G), R17.2
BB_GPIO1: J1.24, MOTOR1_SELECT.P$1, U1.2 (G)
BB_GPIO2: J1.25, MOTOR2_SELECT.P$1, U1.5 (G)
BB_I2C2_SCL: J1.17, J4.2
BB_I2C2_SDA: J1.18, J4.3
BB_I2C3_SCL: BB_I2C3_SCL.P$1, J1.9, J6.2, U12.1 (SCL)
BB_I2C3_SDA: BB_I2C3_SDA.P$1, J1.10, J6.3, U12.3 (SDA)
BB_UART5_RX: J1.16, U$47.1 (B2)
BB_UART5_TX: J1.15, U$47.8 (B1)
BB_USART1_RX: BB_USART1_RX.P$1, J1.8, J10.RX, U9.5 (G), U$4.2 (DOUT)
BB_USART1_TX: BB_USART1_TX.P$1, J1.7, J10.TX, U9.2 (G), U$4.3 (DIN)
BB_USART2_CTS: J1.19, MOTOR3_SELECT.P$1, U2.2 (G)
BB_USART2_RTS: J1.20, MOTOR4_SELECT.P$1, U2.5 (G)
BB_USART2_TX: BB_USART2_TX.P$1, J1.21, U3.2 (G), U4.2 (G), U5.2 (G), U6.2 (G)
GND: C1.2, C2.2, C3.2, C4.2, C5.2, C6.2, C7.C (-), C8.2, C9.C (-), C11.C (-), GND.1, GND..1, GND_GND.P$1, J1.3, J1.4, J1.27, J2.3, J3.3 (GND), J4.4, J5.5, J6.4, J7.6, J8.1, J8.3, J8.5, J8.7, J10.GND, J12.3 (GND), J13.3 (GND), LED1.C, Q1.1 (G), Q2.2 (S), R10.1, R11.1, R12.2, R16.1, R17.1, R20.2, S2.1 (O), SSR1.2, U1.1 (S), U1.4 (S), U2.1 (S), U2.4 (S), U3.1 (S), U3.4 (S), U4.1 (S), U4.4 (S), U5.1 (S), U5.4 (S), U6.1 (S), U6.4 (S), U7.1 (S), U7.4 (S), U8.1 (S), U8.4 (S), U10.2 (GND), U11.1 (GND(ADJ)), U12.2 (VSS), U13.2 (GND), U$4.10 (GND), U$47.2 (GND)
MOTOR1_IRQ: J09.10, U7.2 (G)
MOTOR1_TX: J09.11, MOTOR1_TX.P$1, R2.2, U3.3 (D)
MOTOR2_IRQ: J09.7, U7.5 (G)
MOTOR2_TX: J09.8, MOTOR2_TX.P$1, R4.2, U4.3 (D)
MOTOR3_IRQ: J09.4, U8.2 (G)
MOTOR3_TX: J09.5, MOTOR3_TX.P$1, R6.2, U5.3 (D)
MOTOR4_IRQ: J09.1, U8.5 (G)
MOTOR4_TX: J09.2, MOTOR4_TX.P$1, R8.2, U6.3 (D)
MOTOR_IRQ: J1.6, R14.2, U7.3 (D), U7.6 (D), U8.3 (D), U8.6 (D)
unnamed: LED1.A, R9.1
unnamed: LED2.C, R10.2
unnamed: LED2.A, U9.3 (D)
unnamed: 6-16V.1, S2.3 (S)
unnamed: LED3.A, U9.6 (D)
unnamed: LED3.C, R11.2
unnamed: Q2.3 (D), R21.1, SG1.-
unnamed: JP1.2, L2.1
unnamed: R16.2, U10.4 (ADJ)
unnamed: J7.5, SSR1.3
unnamed: R15.1, SSR1.1
unnamed: J7.3, SSR1.4
unnamed: C6.1, J2.1, L2.2
unnamed: J10.+5V, R18.2
unnamed: BOARD_CFG_WRITE.P$1, R20.1, U12.5 (WP)
unnamed: J5.2, U$47.5 (A1)
unnamed: J5.3, U$47.4 (A2)
unnamed: J2.2, R19.1
PPM_INPUT: J1.23, J3.1 (PPM)
RELAY1: J1.5, R15.2
SERVO1: J1.13, J12.1 (PPM)
SERVO2: J1.14, J13.1 (PPM)
VBAT: C7.A (+), J7.4, J8.2, J8.4, J8.6, J8.8, Q1.3 (S), R21.2, SG1.+, U10.1 (VIN)
VBATM: Q1.4 (D), R13.1, S2.2
VBAT_3V3: C1.1, J1.11, R12.1, R13.2, VBAT_3V3.P$1
VDD_1V8: C9.A (+), JP2.1, U13.5 (OUT)
VDD_3V3: 3.3V.1, C11.A (+), J7.2, JP1.3, JP2.3, JP3.3, R9.2, U9.1 (S), U9.4 (S), U11.2 (VOUT), U11.4 (VOUT-TAB), U12.4 (VCC), U13.1 (IN), U13.3 (EN), U$4.1 (VDD), U$47.6 (OE), U$47.7 (VCCB), VDD_3V3.P$1
VDD_5V: 5V.1, C2.1, C3.1, C4.1, C5.1, J1.1, J1.2, J3.2 (+5V), J4.1, J5.1, J6.1, J7.1, J09.3, J09.6, J09.9, J09.12, J12.2 (+5V), J13.2 (+5V), JP1.1, R1.1, R2.1, R3.1, R4.1, R5.1, R6.1, R7.1, R8.1, R14.1, R18.1, U10.3 (VOUT), U11.3 (VIN), VDD_5V.P$1
V_SHIFT: JP2.2, U$47.3 (VCCA)

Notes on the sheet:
Power Supply
Production testing pads
External I2C 2
Expansion Connector
PPM Input
Mounting Stack
Mounting holes Parrot/IMU
Mounting holes Flow Boards.
Motor Serial Port Driver
LEDs
External UART
XBEE
BUZZER
External I2C 3
Wire pads
Voltage Measurement
RELAY
ANALOG Measurement
EEPROM
PWM
CAN2RX 5V tolerant!
